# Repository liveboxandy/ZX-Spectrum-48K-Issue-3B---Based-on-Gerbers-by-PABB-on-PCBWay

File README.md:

# ZX-Spectrum 48K Issue 3B - Based on Gerbers by PABB on PCBWay

KiCAD created files for the ZX Spectrum 48K Issue 3B designed by Sinclair Research Ltd - Based on PABB Gerbers

Original Gerbers by PABB downloadable via PCBWay.

See https://www.pcbway.com/project/shareproject/ZX_Spectrum_48_Issue_3B_Redrawn.html

Only the gerbers are available on PCBWay. No Schematic.

Schematic created from available schematics with corrections using Service Guide mods and PCB layout. 

Where differences were seen the PCB layout took preference.

This was only done in order to create an assist in debugging.

I would NOT use these gerbers to get a PCB manufactured without a lot more checking first.

For the following ULA 6C001 make the following changes,

R47 to 1K,
R49 to 10K,
R56 to 1K,
R63 to 1K.

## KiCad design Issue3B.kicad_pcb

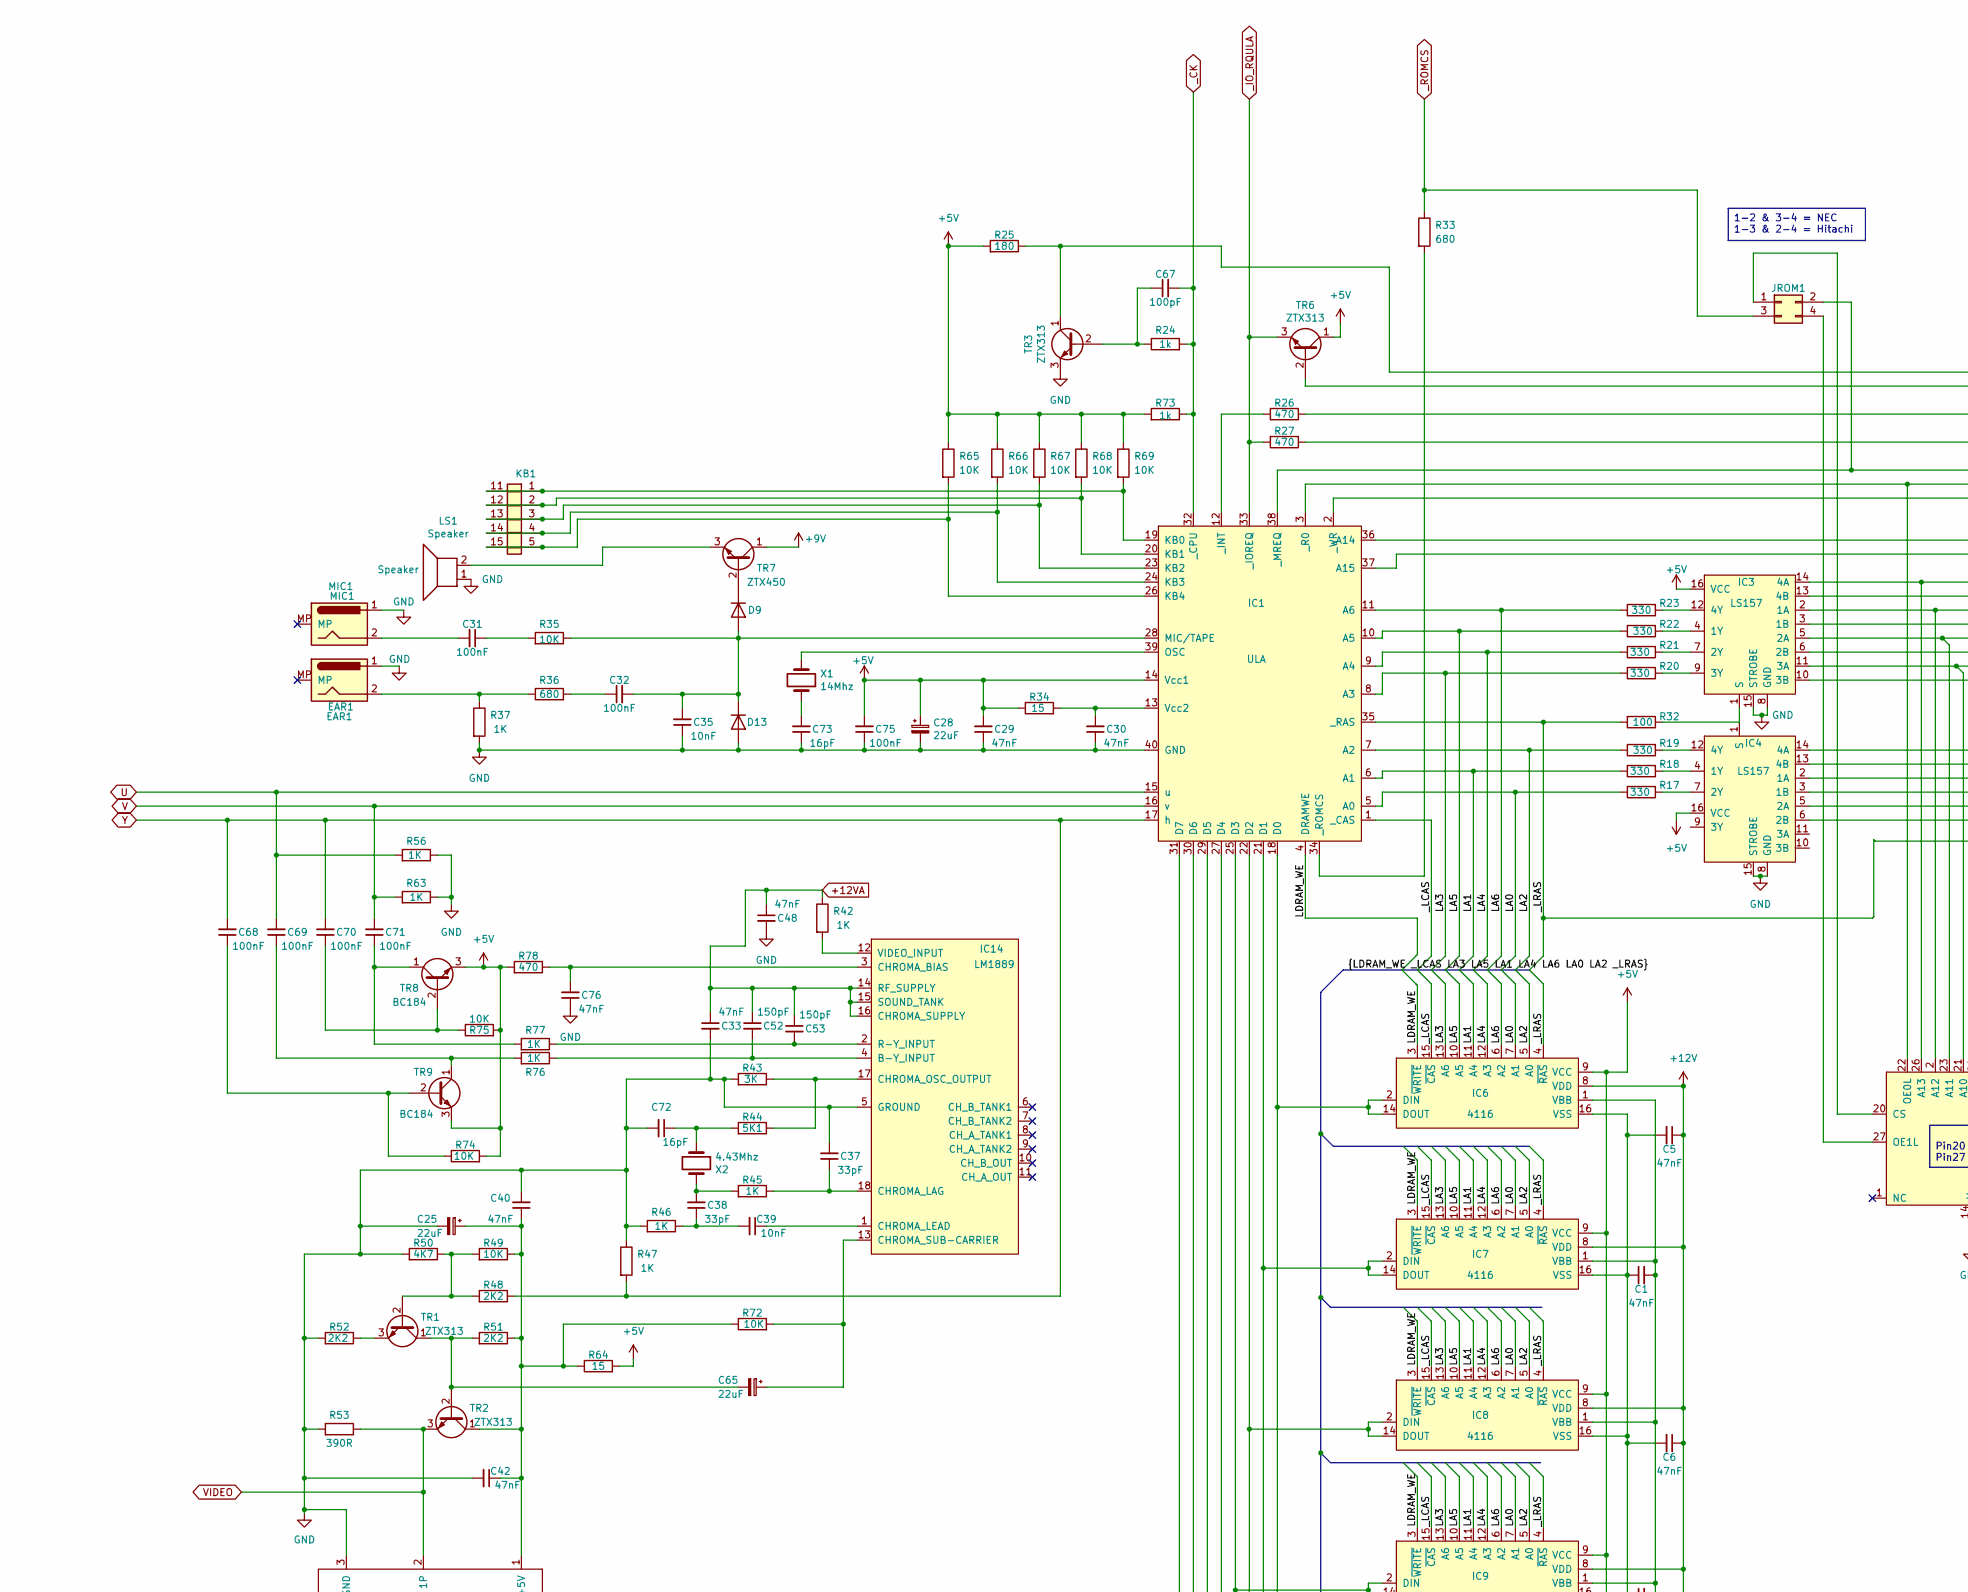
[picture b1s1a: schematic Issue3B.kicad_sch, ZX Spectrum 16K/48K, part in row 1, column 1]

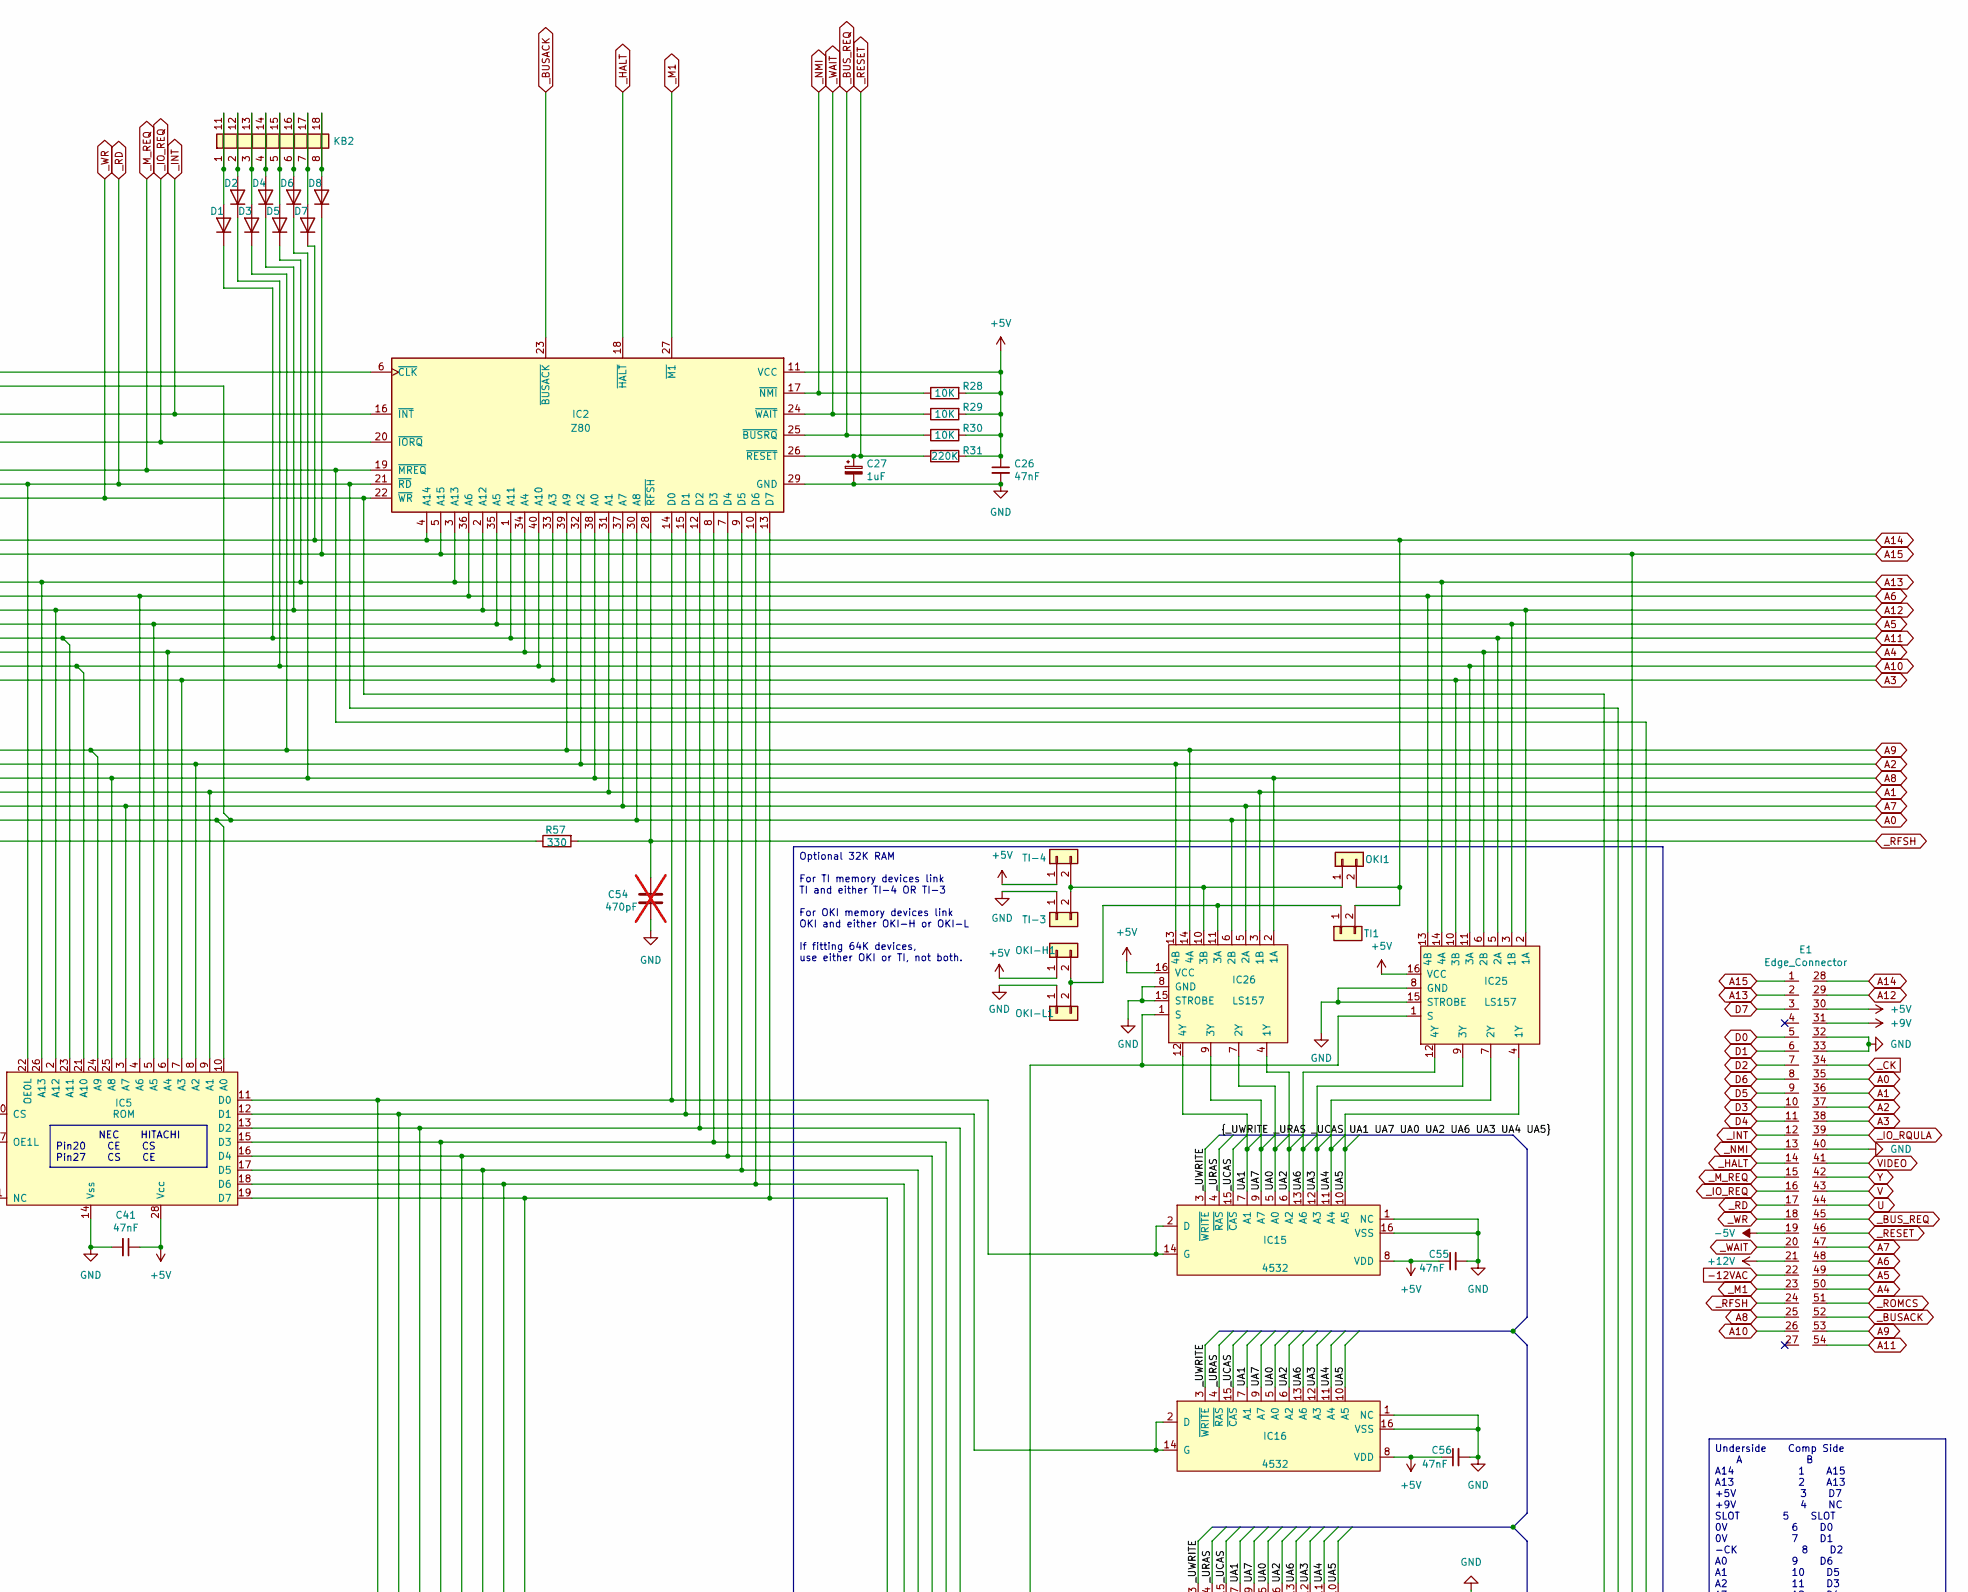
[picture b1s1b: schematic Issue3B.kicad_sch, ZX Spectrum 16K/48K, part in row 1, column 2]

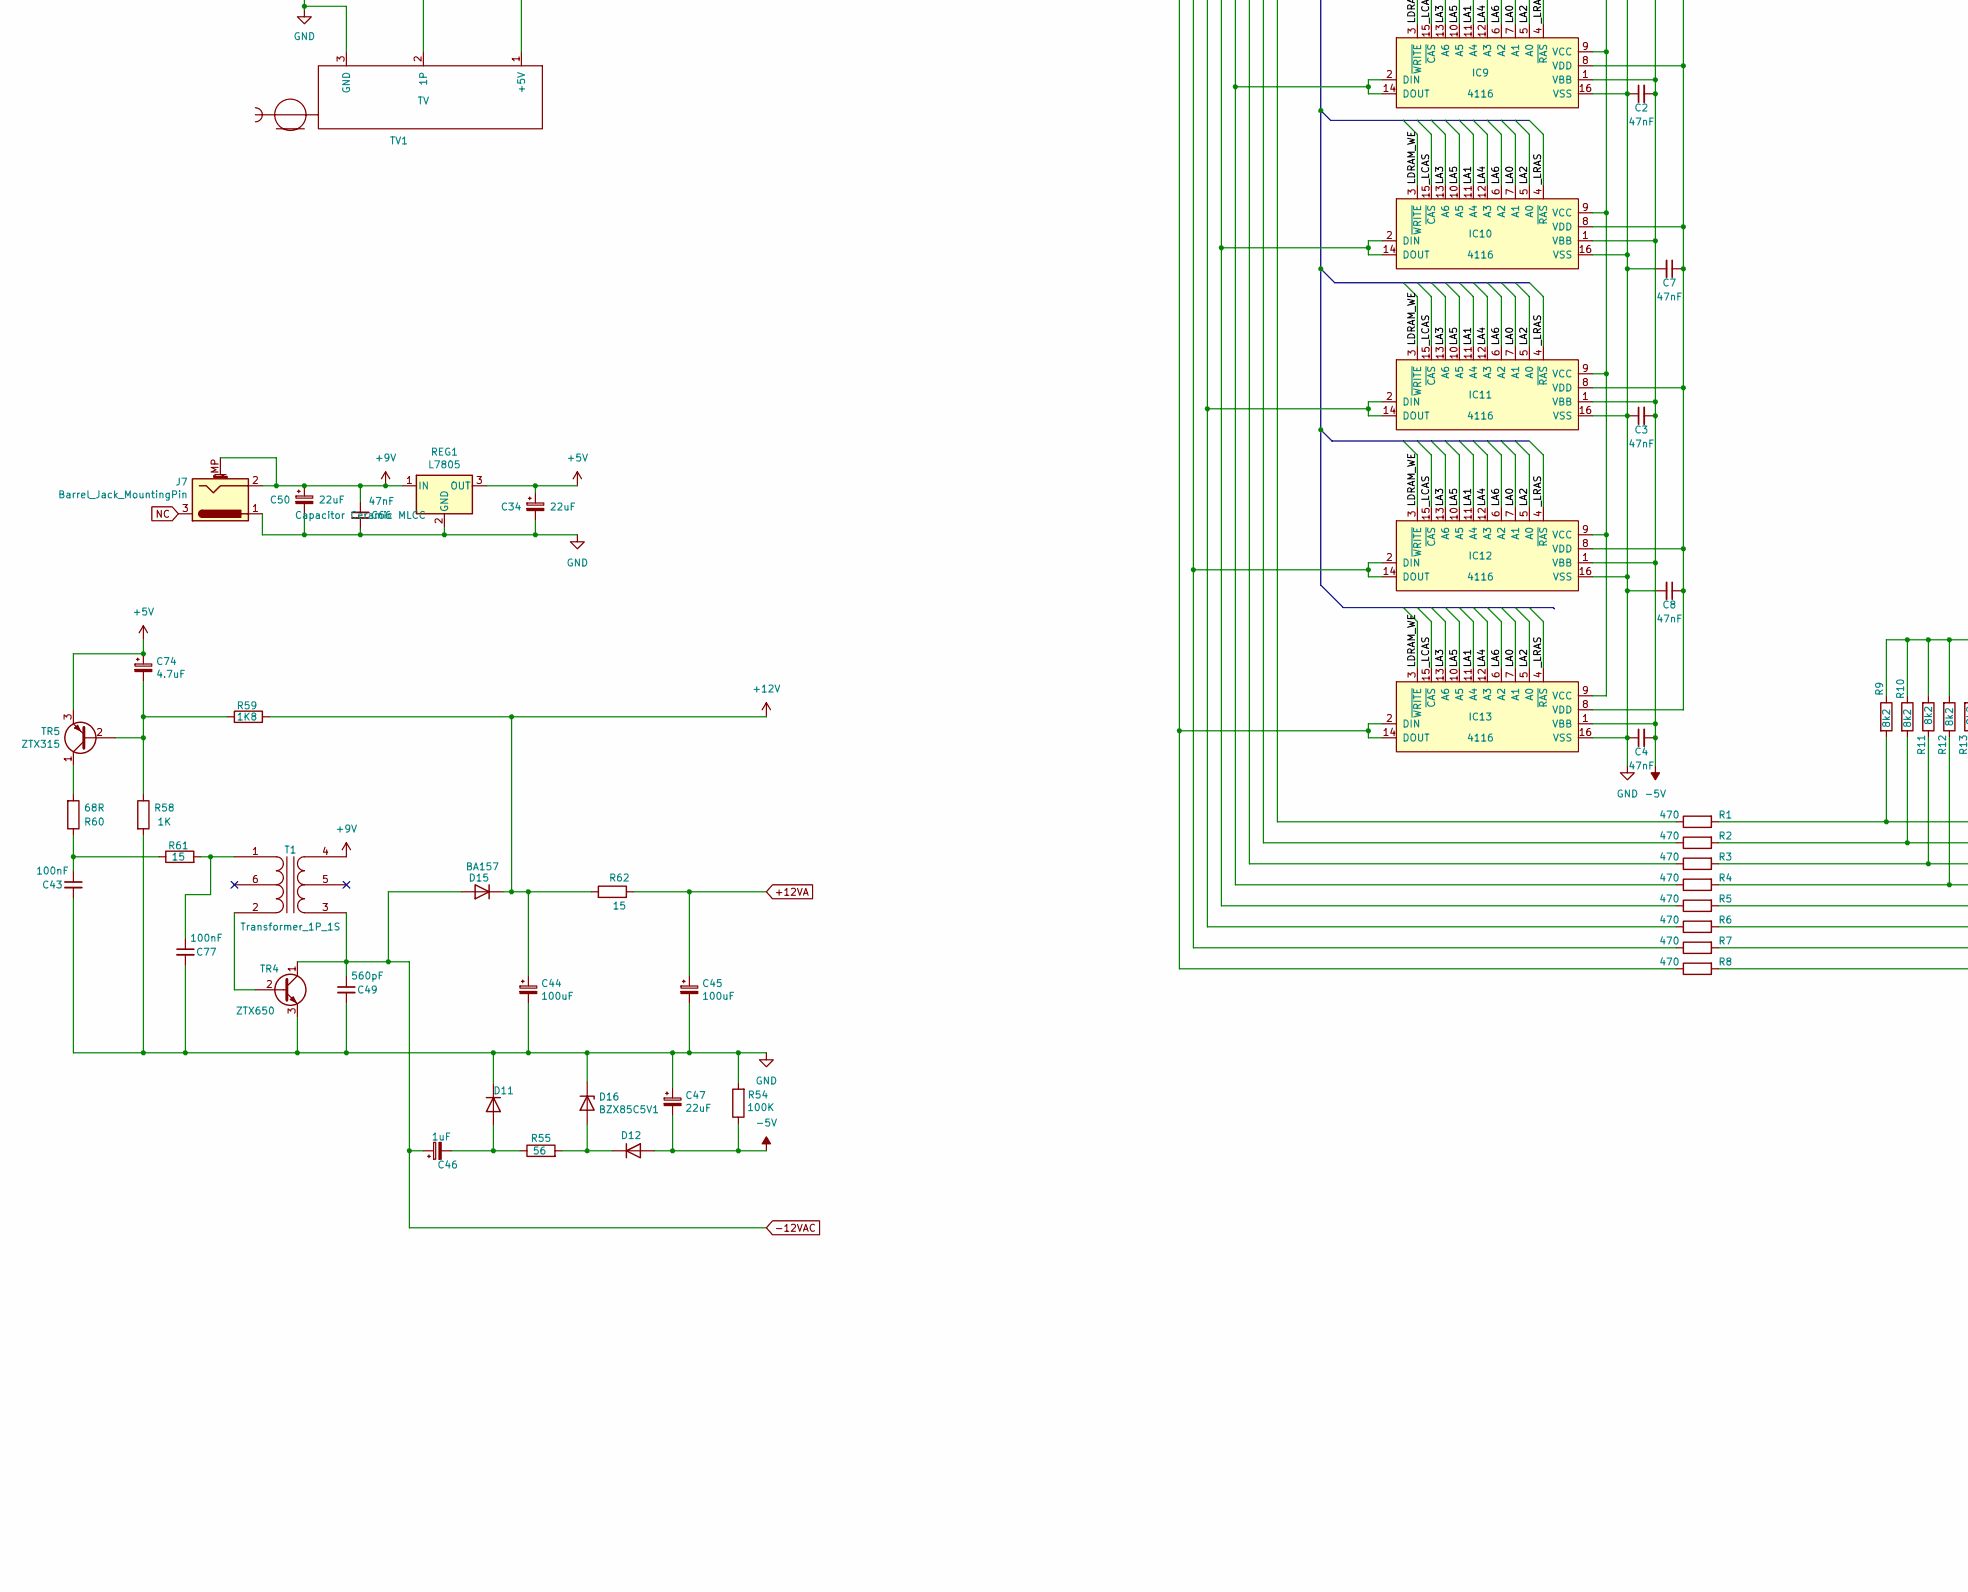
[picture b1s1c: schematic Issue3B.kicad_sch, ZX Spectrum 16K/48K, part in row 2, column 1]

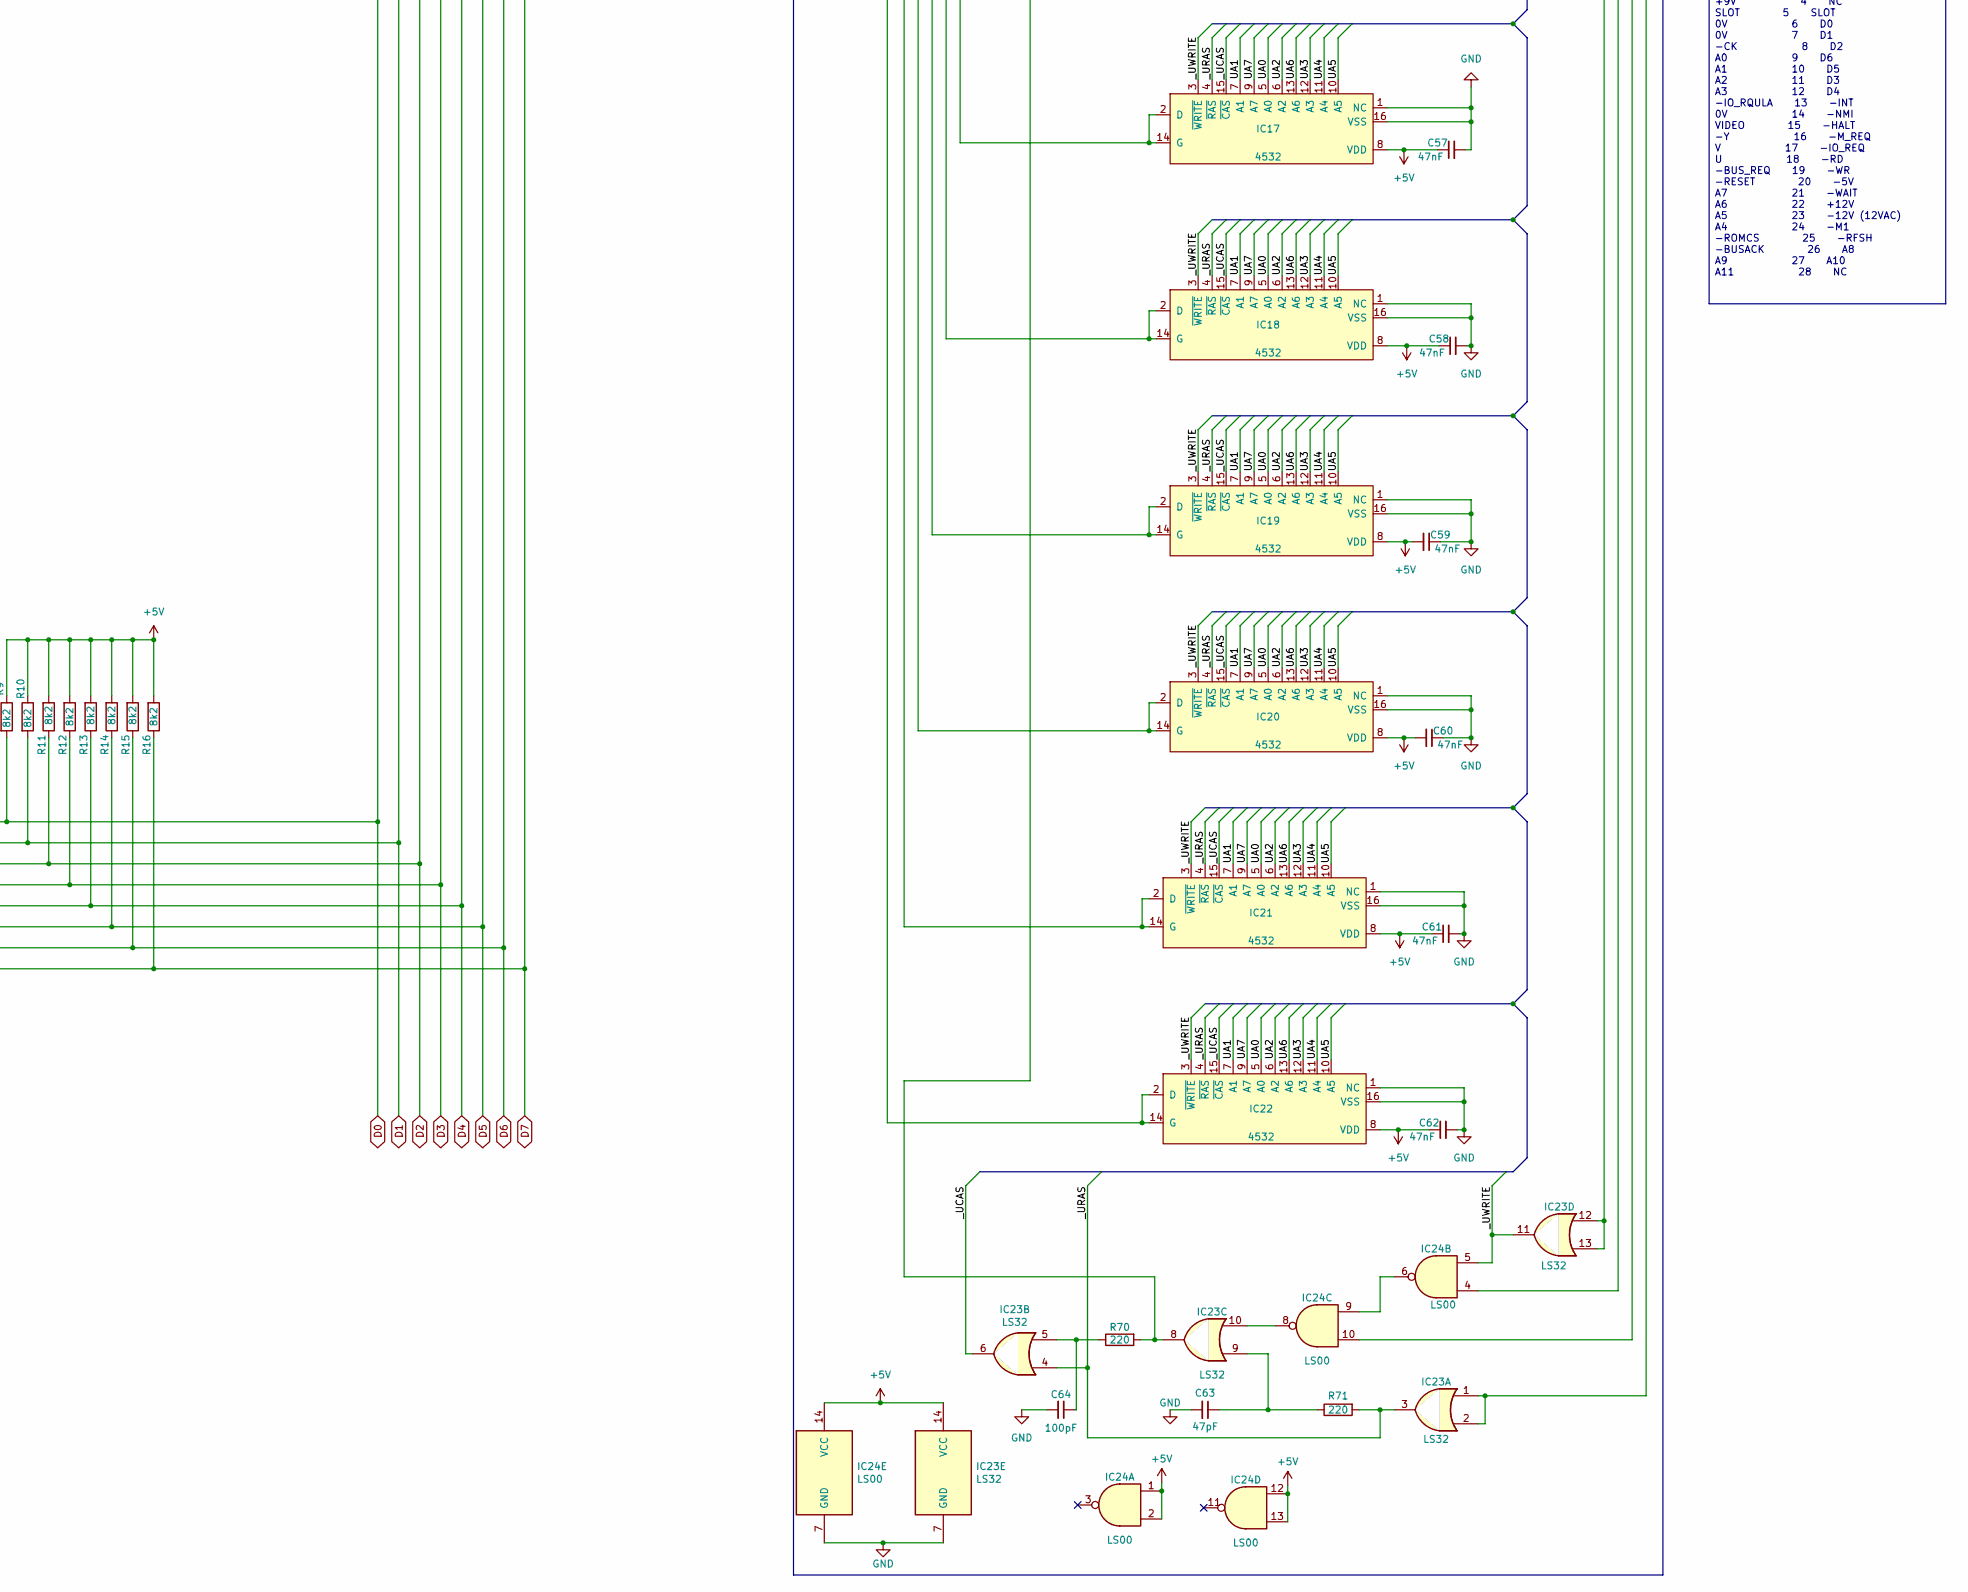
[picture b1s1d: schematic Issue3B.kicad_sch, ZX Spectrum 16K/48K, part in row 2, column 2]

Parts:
C1, C2, C3, C4, C5, C6, C7, C8, C26, C29, C30, C33, C40, C41, C42, C48, C55, C56, C57, C58, C59, C60, C61, C62, C66, C76: 47nF; C_Axial_L3.8mm_D2.6mm_P12.70mm_Horizontal
C25: 22uF; CP_Axial_L11.0mm_D6.0mm_P20.00mm_Horizontal
C27: 1uF; CP_Axial_L11.0mm_D6.0mm_P20.00mm_Horizontal
C28, C34, C47, C50, C65: 22uF; CP_Axial_L11.0mm_D6.0mm_P20.32mm_Horizontal
C31, C32: 100nF; C_Axial_L3.8mm_D2.6mm_P12.40mm_Horizontal
C35: 10nF; C_Axial_L3.8mm_D2.6mm_P12.40mm_Horizontal
C37, C38: 33pF; C_Axial_L3.8mm_D2.6mm_P12.70mm_Horizontal
C39: 10nF; C_Axial_L3.8mm_D2.6mm_P12.70mm_Horizontal
C43, C68, C69, C70, C71, C75, C77: 100nF; C_Axial_L3.8mm_D2.6mm_P12.70mm_Horizontal
C44, C45: 100uF; CP_Axial_L11.0mm_D6.0mm_P20.32mm_Horizontal
C46: 1uF; CP_Axial_L11.0mm_D6.0mm_P20.32mm_Horizontal
C49: 560pF; C_Axial_L3.8mm_D2.6mm_P12.70mm_Horizontal
C52, C53: 150pF; C_Axial_L3.8mm_D2.6mm_P12.70mm_Horizontal
C54: 470pF; C_Axial_L3.8mm_D2.6mm_P12.70mm_Horizontal; not fitted
C63: 47pF; C_Axial_L3.8mm_D2.6mm_P12.70mm_Horizontal
C64, C67: 100pF; C_Axial_L3.8mm_D2.6mm_P12.70mm_Horizontal
C72, C73: 16pF; C_Axial_L3.8mm_D2.6mm_P12.70mm_Horizontal
C74: 4.7uF; CP_Axial_L11.0mm_D6.0mm_P20.32mm_Horizontal
D1, D2, D3, D4, D5, D6, D7, D8, D9, D11, D12: 1N4148; D_DO-35_SOD27_P12.70mm_Horizontal
D13: 1N4148; D_DO-35_SOD27_P12.40mm_Horizontal
D15: BA157; D_DO-35_SOD27_P12.70mm_Horizontal
D16: BZX85C5V1; D_DO-35_SOD27_P12.70mm_Horizontal
E1: Edge_Connector; Edge Connector
EAR1: EAR1; 3.5mm_socket
IC1: ULA; DIP-40_W15.24mm_Socket
IC2: Z80; DIP-40_W15.24mm_Socket
IC3, IC4, IC25, IC26: LS157; DIP-16_W7.62mm_Socket
IC5: ROM; DIP-28_W15.24mm_Socket
IC6, IC7, IC8, IC9, IC10, IC11, IC12, IC13: 4116; DIP-16_W7.62mm_Socket
IC14: LM1889; DIP-18_W7.62mm_Socket
IC15, IC16, IC17, IC18, IC19, IC20, IC21, IC22: 4532; DIP-16_W7.62mm_Socket
IC23: LS32; DIP-14_W7.62mm_Socket
IC24: LS00; DIP-14_W7.62mm_Socket
J7: Barrel_Jack_MountingPin; BarrelJack_Horizontal
JROM1: JROM; ROM_WireLink
KB1: Keyboard5
KB2: Keyboard8
LS1: Speaker
MIC1: MIC1; 3.5mm_socket
OKI1: OKI; WireLink
OKI-H1: OKI-H; WireLink
OKI-L1: OKI-L; WireLink
R1, R2, R3, R4, R5, R6, R7, R8, R26, R27, R78: 470; R_Yageo_L3.6mm_D1.6mm_P12.70mm_Horizontal
R9, R10, R11, R12, R13, R14, R15, R16: 8k2; R_Yageo_L3.6mm_D1.6mm_P12.70mm_Horizontal
R17, R18, R19, R20, R21, R22, R23, R57: 330; R_Yageo_L3.6mm_D1.6mm_P12.70mm_Horizontal
R24, R73: 1k; R_Yageo_L3.6mm_D1.6mm_P12.70mm_Horizontal
R25: 180; R_Yageo_L3.6mm_D1.6mm_P12.70mm_Horizontal
R28, R29, R30, R49, R65, R66, R67, R68, R69, R72, R74, R75: 10K; R_Yageo_L3.6mm_D1.6mm_P12.70mm_Horizontal
R31: 220K; R_Yageo_L3.6mm_D1.6mm_P12.70mm_Horizontal
R32: 100; R_Yageo_L3.6mm_D1.6mm_P12.70mm_Horizontal
R33: 680; R_Yageo_L3.6mm_D1.6mm_P12.70mm_Horizontal
R34: 15; R_Axial_DIN0516_L15.5mm_D5.0mm_P22.60mm_Horizontal
R35: 10K; R_Yageo_L3.6mm_D1.6mm_P12.40mm_Horizontal
R36: 680; R_Yageo_L3.6mm_D1.6mm_P12.40mm_Horizontal
R37: 1K; R_Yageo_L3.6mm_D1.6mm_P12.40mm_Horizontal
R42, R45, R46, R47, R56, R58, R63, R76, R77: 1K; R_Yageo_L3.6mm_D1.6mm_P12.70mm_Horizontal
R43: 3K; R_Yageo_L3.6mm_D1.6mm_P12.70mm_Horizontal
R44: 5K1; R_Yageo_L3.6mm_D1.6mm_P12.70mm_Horizontal
R48, R51, R52: 2K2; R_Yageo_L3.6mm_D1.6mm_P12.70mm_Horizontal
R50: 4K7; R_Yageo_L3.6mm_D1.6mm_P12.70mm_Horizontal
R53: 390R; R_Yageo_L3.6mm_D1.6mm_P12.70mm_Horizontal
R54: 100K; R_Yageo_L3.6mm_D1.6mm_P12.70mm_Horizontal
R55: 56; R_Yageo_L3.6mm_D1.6mm_P12.70mm_Horizontal
R59: 1K8; R_Yageo_L3.6mm_D1.6mm_P12.70mm_Horizontal
R60: 68R; R_Yageo_L3.6mm_D1.6mm_P12.70mm_Horizontal
R61, R62, R64: 15; R_Yageo_L3.6mm_D1.6mm_P12.70mm_Horizontal
R70, R71: 220; R_Yageo_L3.6mm_D1.6mm_P12.70mm_Horizontal
REG1: L7805; TO-220-3_Horizontal_TabDown
T1: Transformer_1P_1S; Coil
TI1: TI; WireLink
TI-3: TI-3; WireLink
TI-4: TI-4; WireLink
TR1, TR2, TR3, TR6: ZTX313; TO-92Flat
TR4: ZTX650; TO-92Flat
TR5: ZTX315; TO-92Flat
TR7: ZTX450; TO-92Flat
TR8, TR9: BC184; TR9
TV1: TV; Modulator
X1: 14Mhz; X1
X2: 4.43Mhz; X2

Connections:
+5V: C26.1, C28.1, C29.2, C34.1, C41.1, C55.1, C56.1, C57.1, C58.1, C59.2, C60.2, C61.1, C62.1, C74.1, C75.2, E1.30, IC1.14 (Vcc1), IC2.11 (VCC), IC3.16 (VCC), IC4.16 (VCC), IC5.28 (Vcc), IC6.9 (VCC), IC7.9 (VCC), IC8.9 (VCC), IC9.9 (VCC), IC10.9 (VCC), IC11.9 (VCC), IC12.9 (VCC), IC13.9 (VCC), IC15.8 (VDD), IC16.8 (VDD), IC17.8 (VDD), IC18.8 (VDD), IC19.8 (VDD), IC20.8 (VDD), IC21.8 (VDD), IC22.8 (VDD), IC23.14 (VCC), IC24.1, IC24.2, IC24.12, IC24.13, IC24.14 (VCC), IC25.16 (VCC), IC26.16 (VCC), OKI-H1.1, R9.1, R10.1, R11.2, R12.2, R13.2, R14.2, R15.2, R16.2, R25.2, R28.2, R29.2, R30.2, R31.1, R34.1, R64.2, R65.1, R66.1, R67.1, R68.1, R69.1, R73.2, R74.2, R75.2, R78.2, REG1.3 (OUT), TI-4.1, TR5.3 (E), TR6.1 (C), TR8.3 (E), TR9.3 (E)
+9V: C50.1, C66.1, E1.31, J7.2, J7.MP (MountPin), REG1.1 (IN), T1.4 (SB), TR7.1 (C)
+12V: C5.1, C6.1, C7.1, C8.1, C44.1, D15.1 (K), E1.21, IC6.8 (VDD), IC7.8 (VDD), IC8.8 (VDD), IC9.8 (VDD), IC10.8 (VDD), IC11.8 (VDD), IC12.8 (VDD), IC13.8 (VDD), R59.2, R62.2
+12VA: C33.1, C45.1, C48.1, C52.1, C53.1, IC14.14 (RF_SUPPLY), IC14.15 (SOUND_TANK), IC14.16 (CHROMA_SUPPLY), R42.1, R62.1
-5V: C1.2, C2.2, C3.2, C4.2, C47.2, D12.2 (A), E1.19, IC6.1 (VBB), IC7.1 (VBB), IC8.1 (VBB), IC9.1 (VBB), IC10.1 (VBB), IC11.1 (VBB), IC12.1 (VBB), IC13.1 (VBB), R54.1
-12VAC: C46.1, C49.1, D15.2 (A), E1.22, T1.3 (SA), TR4.1 (C)
/LA0: IC1.5 (A0), IC6.7 (A1), IC7.7 (A1), IC8.7 (A1), IC9.7 (A1), IC10.7 (A1), IC11.7 (A1), IC12.7 (A1), IC13.7 (A1), R17.1
/LA1: IC1.6 (A1), IC6.11 (A4), IC7.11 (A4), IC8.11 (A4), IC9.11 (A4), IC10.11 (A4), IC11.11 (A4), IC12.11 (A4), IC13.11 (A4), R18.1
/LA2: IC1.7 (A2), IC6.5 (A0), IC7.5 (A0), IC8.5 (A0), IC9.5 (A0), IC10.5 (A0), IC11.5 (A0), IC12.5 (A0), IC13.5 (A0), R19.1
/LA3: IC1.8 (A3), IC6.13 (A6), IC7.13 (A6), IC8.13 (A6), IC9.13 (A6), IC10.13 (A6), IC11.13 (A6), IC12.13 (A6), IC13.13 (A6), R20.1
/LA4: IC1.9 (A4), IC6.12 (A3), IC7.12 (A3), IC8.12 (A3), IC9.12 (A3), IC10.12 (A3), IC11.12 (A3), IC12.12 (A3), IC13.12 (A3), R21.1
/LA5: IC1.10 (A5), IC6.10 (A5), IC7.10 (A5), IC8.10 (A5), IC9.10 (A5), IC10.10 (A5), IC11.10 (A5), IC12.10 (A5), IC13.10 (A5), R22.1
/LA6: IC1.11 (A6), IC6.6 (A2), IC7.6 (A2), IC8.6 (A2), IC9.6 (A2), IC10.6 (A2), IC11.6 (A2), IC12.6 (A2), IC13.6 (A2), R23.1
/LDRAM_WE: IC1.4 (DRAMWE), IC6.3 (~WRITE), IC7.3 (~WRITE), IC8.3 (~WRITE), IC9.3 (~WRITE), IC10.3 (~WRITE), IC11.3 (~WRITE), IC12.3 (~WRITE), IC13.3 (~WRITE)
/UA0: IC15.5 (A0), IC16.5 (A0), IC17.5 (A0), IC18.5 (A0), IC19.5 (A0), IC20.5 (A0), IC21.5 (A0), IC22.5 (A0), IC26.7 (2Y)
/UA1: IC15.7 (A1), IC16.7 (A1), IC17.7 (A1), IC18.7 (A1), IC19.7 (A1), IC20.7 (A1), IC21.7 (A1), IC22.7 (A1), IC26.12 (4Y)
/UA2: IC15.6 (A2), IC16.6 (A2), IC17.6 (A2), IC18.6 (A2), IC19.6 (A2), IC20.6 (A2), IC21.6 (A2), IC22.6 (A2), IC26.4 (1Y)
/UA3: IC15.12 (A3), IC16.12 (A3), IC17.12 (A3), IC18.12 (A3), IC19.12 (A3), IC20.12 (A3), IC21.12 (A3), IC22.12 (A3), IC25.9 (3Y)
/UA4: IC15.11 (A4), IC16.11 (A4), IC17.11 (A4), IC18.11 (A4), IC19.11 (A4), IC20.11 (A4), IC21.11 (A4), IC22.11 (A4), IC25.7 (2Y)
/UA5: IC15.10 (A5), IC16.10 (A5), IC17.10 (A5), IC18.10 (A5), IC19.10 (A5), IC20.10 (A5), IC21.10 (A5), IC22.10 (A5), IC25.4 (1Y)
/UA6: IC15.13 (A6), IC16.13 (A6), IC17.13 (A6), IC18.13 (A6), IC19.13 (A6), IC20.13 (A6), IC21.13 (A6), IC22.13 (A6), IC25.12 (4Y)
/UA7: IC15.9 (A7), IC16.9 (A7), IC17.9 (A7), IC18.9 (A7), IC19.9 (A7), IC20.9 (A7), IC21.9 (A7), IC22.9 (A7), IC26.9 (3Y)
/_LCAS: IC1.1 (_CAS), IC6.15 (~CAS), IC7.15 (~CAS), IC8.15 (~CAS), IC9.15 (~CAS), IC10.15 (~CAS), IC11.15 (~CAS), IC12.15 (~CAS), IC13.15 (~CAS)
/_LRAS: IC1.35 (_RAS), IC6.4 (~RAS), IC7.4 (~RAS), IC8.4 (~RAS), IC9.4 (~RAS), IC10.4 (~RAS), IC11.4 (~RAS), IC12.4 (~RAS), IC13.4 (~RAS), R32.2, R57.1
/_UCAS: IC15.15 (~CAS), IC16.15 (~CAS), IC17.15 (~CAS), IC18.15 (~CAS), IC19.15 (~CAS), IC20.15 (~CAS), IC21.15 (~CAS), IC22.15 (~CAS), IC23.6
/_URAS: IC15.4 (~RAS), IC16.4 (~RAS), IC17.4 (~RAS), IC18.4 (~RAS), IC19.4 (~RAS), IC20.4 (~RAS), IC21.4 (~RAS), IC22.4 (~RAS), IC23.3, IC23.4, R71.2
/_UWRITE: IC15.3 (~WRITE), IC16.3 (~WRITE), IC17.3 (~WRITE), IC18.3 (~WRITE), IC19.3 (~WRITE), IC20.3 (~WRITE), IC21.3 (~WRITE), IC22.3 (~WRITE), IC23.11, IC24.5
A0: E1.35, IC2.30 (A8), IC4.6 (2B), IC5.10 (A0), IC26.6 (2B), TR6.2 (B)
A1: E1.36, IC2.31 (A1), IC4.3 (1B), IC5.9 (A1), IC26.3 (1B)
A2: E1.37, IC2.32 (A2), IC4.13 (4B), IC5.8 (A2), IC26.13 (4B)
A3: E1.38, IC2.33 (A3), IC3.10 (3B), IC5.7 (A3), IC25.10 (3B)
A4: E1.50, IC2.34 (A4), IC3.6 (2B), IC5.6 (A4), IC25.6 (2B)
A5: E1.49, IC2.35 (A5), IC3.3 (1B), IC5.5 (A5), IC25.3 (1B)
A6: E1.48, IC2.36 (A6), IC3.13 (4B), IC5.4 (A6), IC25.13 (4B)
A7: E1.47, IC2.37 (A7), IC4.5 (2A), IC5.3 (A7), IC26.5 (2A)
A8: D6.1 (K), E1.25, IC2.38 (A0), IC4.2 (1A), IC5.25 (A8), IC26.2 (1A)
A9: D3.1 (K), E1.53, IC2.39 (A9), IC4.14 (4A), IC5.24 (A9), IC26.14 (4A)
A10: D2.1 (K), E1.26, IC2.40 (A10), IC3.11 (3A), IC5.21 (A10), IC25.11 (3A)
A11: D1.1 (K), E1.54, IC2.1 (A11), IC3.5 (2A), IC5.23 (A11), IC25.5 (2A)
A12: D4.1 (K), E1.29, IC2.2 (A12), IC3.2 (1A), IC5.2 (A12), IC25.2 (1A)
A13: D5.1 (K), E1.2, IC2.3 (A13), IC3.14 (4A), IC5.26 (A13), IC25.14 (4A)
A14: D7.1 (K), E1.28, IC1.36 (A14), IC2.4 (A14), OKI1.2, TI1.2
A15: D8.1 (K), E1.1, IC1.37 (A15), IC2.5 (A15), IC24.10
D0: E1.5, IC2.14 (D0), IC5.11 (D0), IC15.2 (D), IC15.14 (G), R1.2, R9.2
D1: E1.6, IC2.15 (D1), IC5.12 (D1), IC16.2 (D), IC16.14 (G), R2.2, R10.2
D2: E1.7, IC2.12 (D2), IC5.13 (D2), IC17.2 (D), IC17.14 (G), R3.2, R11.1
D3: E1.10, IC2.8 (D3), IC5.15 (D3), IC18.2 (D), IC18.14 (G), R4.2, R12.1
D4: E1.11, IC2.7 (D4), IC5.16 (D4), IC19.2 (D), IC19.14 (G), R5.2, R13.1
D5: E1.9, IC2.9 (D5), IC5.17 (D5), IC20.2 (D), IC20.14 (G), R6.2, R14.1
D6: E1.8, IC2.10 (D6), IC5.18 (D6), IC21.2 (D), IC21.14 (G), R7.2, R15.1
D7: E1.3, IC2.13 (D7), IC5.19 (D7), IC22.2 (D), IC22.14 (G), R8.2, R16.1
GND: C1.1, C2.1, C3.1, C4.1, C5.2, C6.2, C7.2, C8.2, C25.2, C26.2, C27.2, C28.2, C29.1, C30.1, C33.2, C34.2, C35.1, C37.2, C40.2, C41.2, C42.2, C43.2, C44.2, C45.2, C47.1, C48.2, C49.2, C50.2, C54.2, C55.2, C56.2, C57.2, C58.2, C59.1, C60.1, C61.2, C62.2, C63.2, C64.2, C66.2, C72.2, C73.1, C75.1, C76.1, C77.2, D11.1 (K), D13.2 (A), D16.1 (K), E1.32, E1.33, E1.40, EAR1.1, IC1.40 (GND), IC2.29 (GND), IC3.8 (GND), IC3.15 (STROBE), IC4.8 (GND), IC4.15 (STROBE), IC5.14 (Vss), IC6.16 (VSS), IC7.16 (VSS), IC8.16 (VSS), IC9.16 (VSS), IC10.16 (VSS), IC11.16 (VSS), IC12.16 (VSS), IC13.16 (VSS), IC14.5 (GROUND), IC15.1 (NC), IC15.16 (VSS), IC16.1 (NC), IC16.16 (VSS), IC17.1 (NC), IC17.16 (VSS), IC18.1 (NC), IC18.16 (VSS), IC19.1 (NC), IC19.16 (VSS), IC20.1 (NC), IC20.16 (VSS), IC21.1 (NC), IC21.16 (VSS), IC22.1 (NC), IC22.16 (VSS), IC23.7 (GND), IC24.7 (GND), IC25.8 (GND), IC25.15 (STROBE), IC26.8 (GND), IC26.15 (STROBE), J7.1, LS1.1, MIC1.1, OKI-L1.1, R37.2, R43.2, R46.2, R47.1, R50.2, R52.2, R53.2, R54.2, R56.1, R58.2, R63.1, REG1.2 (GND), TI-3.1, TR3.3 (E), TR4.3 (E), TV1.3 (GND)
NC: J7.3 (MP2)
unnamed: C31.1, R35.2
unnamed: C31.2, MIC1.2
unnamed: C32.1, R36.2
unnamed: C38.1, C39.2, R46.1
unnamed: C38.2, R45.2, X2.2
unnamed: C43.1, R60.1, R61.1
unnamed: C63.1, IC23.9, R71.1
unnamed: C64.1, IC23.5, R70.1
unnamed: C72.1, R44.2, X2.1
unnamed: C73.2, X1.1
unnamed: D1.2 (A), KB2.1, KB2.11 (Pin_1A)
unnamed: D2.2 (A), KB2.2, KB2.12 (Pin_2A)
unnamed: D3.2 (A), KB2.3, KB2.13 (Pin_3A)
unnamed: D4.2 (A), KB2.4, KB2.14 (Pin_4A)
unnamed: D5.2 (A), KB2.5, KB2.15 (Pin_5A)
unnamed: D6.2 (A), KB2.6, KB2.16 (Pin_6A)
unnamed: D7.2 (A), KB2.7, KB2.17 (Pin_7A)
unnamed: D8.2 (A), KB2.8, KB2.18 (Pin_8A)
unnamed: D9.1 (K), TR7.2 (B)
unnamed: C46.2, D11.2 (A), R55.1
unnamed: D12.1 (K), D16.2 (A), R55.2
unnamed: C32.2, C35.2, D9.2 (A), D13.1 (K), IC1.28 (MIC/TAPE), R35.1
unnamed: EAR1.2, R36.1, R37.1
unnamed: IC1.18 (D0), IC6.2 (DIN), IC6.14 (DOUT), R1.1
unnamed: IC1.21 (D1), IC7.2 (DIN), IC7.14 (DOUT), R2.1
unnamed: IC1.22 (D2), IC8.2 (DIN), IC8.14 (DOUT), R3.1
unnamed: IC1.25 (D3), IC9.2 (DIN), IC9.14 (DOUT), R4.1
unnamed: IC1.27 (D4), IC10.2 (DIN), IC10.14 (DOUT), R5.1
unnamed: IC1.29 (D5), IC11.2 (DIN), IC11.14 (DOUT), R6.1
unnamed: IC1.30 (D6), IC12.2 (DIN), IC12.14 (DOUT), R7.1
unnamed: IC1.31 (D7), IC13.2 (DIN), IC13.14 (DOUT), R8.1
unnamed: IC1.19 (KB0), KB1.1, KB1.11 (A1), R69.2
unnamed: IC1.20 (KB1), KB1.2, KB1.12 (2A), R68.2
unnamed: IC1.23 (KB2), KB1.3, KB1.13 (3A), R67.2
unnamed: IC1.24 (KB3), KB1.4, KB1.14 (4A), R66.2
unnamed: IC1.26 (KB4), KB1.5, KB1.15 (5A), R65.2
unnamed: IC1.39 (OSC), X1.2
unnamed: C30.2, IC1.13 (Vcc2), R34.2
unnamed: IC1.12 (_INT), R26.1
unnamed: IC1.34 (_ROMCS), R33.2
unnamed: IC2.6 (~CLK), R25.1, TR3.1 (C)
unnamed: IC3.4 (1Y), R22.2
unnamed: IC3.7 (2Y), R21.2
unnamed: IC3.9 (3Y), R20.2
unnamed: IC3.12 (4Y), R23.2
unnamed: IC3.1 (S), IC4.1 (S), R32.1
unnamed: IC4.4 (1Y), R18.2
unnamed: IC4.7 (2Y), R17.2
unnamed: IC4.12 (4Y), R19.2
unnamed: IC5.20 (CS), JROM1.1
unnamed: IC5.27 (OE1L), JROM1.4
unnamed: C52.2, IC14.4 (B-Y_INPUT), R76.1
unnamed: C76.2, IC14.3 (CHROMA_BIAS), R78.1
unnamed: C37.1, IC14.18 (CHROMA_LAG), R45.1
unnamed: C39.1, IC14.1 (CHROMA_LEAD)
unnamed: IC14.17 (CHROMA_OSC_OUTPUT), R43.1, R44.1
unnamed: C65.1, IC14.13 (CHROMA_SUB-CARRIER), R72.2
unnamed: C53.2, IC14.2 (R-Y_INPUT), R77.1
unnamed: IC14.12 (VIDEO_INPUT), R42.2
unnamed: IC23.10, IC24.8
unnamed: IC24.6, IC24.9
unnamed: IC23.8, IC25.1 (S), IC26.1 (S), R70.2
unnamed: IC26.11 (3A), OKI-H1.2, OKI-L1.2, TI1.1
unnamed: IC26.10 (3B), OKI1.1, TI-3.2, TI-4.2
unnamed: C77.1, R61.2, T1.1 (AA)
unnamed: T1.2 (AB), TR4.2 (B)
unnamed: R48.2, R49.2, R50.1, TR1.2 (B)
unnamed: C65.2, R51.2, TR1.1 (C), TR2.2 (B)
unnamed: R52.1, TR1.3 (E)
unnamed: C25.1, C40.1, C42.1, R49.1, R51.1, R64.1, R72.1, TR2.1 (C), TV1.1 (+5V)
unnamed: C67.1, R24.1, TR3.2 (B)
unnamed: C74.2, R58.1, R59.1, TR5.2 (B)
unnamed: R60.2, TR5.1 (C)
unnamed: LS1.2, TR7.3 (E)
unnamed: C70.1, R75.1, TR8.2 (B)
unnamed: C71.1, R77.2, TR8.1 (C)
unnamed: C68.1, R74.1, TR9.2 (B)
unnamed: C69.1, R76.2, TR9.1 (C)
U: C69.2, E1.44, IC1.15 (u), R56.2
V: C71.2, E1.43, IC1.16 (v), R63.2
VIDEO: E1.41, R53.1, TR2.3 (E), TV1.2 (1P)
Y: C68.2, C70.2, E1.42, IC1.17 (h), R47.2, R48.1
_BUSACK: E1.52, IC2.23 (~BUSACK)
_BUS_REQ: E1.45, IC2.25 (~BUSRQ), R30.1
_CK: C67.2, E1.34, IC1.32 (_CPU), R24.2, R73.1
_HALT: E1.14, IC2.18 (~HALT)
_INT: E1.12, IC2.16 (~INT), R26.2
_IO_REQ: E1.16, IC2.20 (~IORQ), R27.2
_IO_RQULA: E1.39, IC1.33 (_IOREQ), R27.1, TR6.3 (E)
_M1: E1.23, IC2.27 (~M1)
_M_REQ: E1.15, IC1.38 (_MREQ), IC2.19 (~MREQ), IC23.1, IC23.2, JROM1.2
_NMI: E1.13, IC2.17 (~NMI), R28.1
_RD: E1.17, IC1.3 (_R0), IC2.21 (~RD), IC5.22 (OE0L), IC24.4
_RESET: C27.1, E1.46, IC2.26 (~RESET), R31.2
_RFSH: C54.1, E1.24, IC2.28 (~RFSH), R57.2
_ROMCS: E1.51, JROM1.3, R33.1
_WAIT: E1.20, IC2.24 (~WAIT), R29.1
_WR: E1.18, IC1.2 (_WR), IC2.22 (~WR), IC23.12, IC23.13

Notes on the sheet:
Optional 32K RAM For TI memory devices link TI and either TI-4 OR TI-3 For OKI memory devices link OKI and either OKI-H or OKI-L If fitting 64K devices, use either OKI or TI, not both.
NEC HITACHI Pin20 CE CS Pin27 CS CE
Underside Comp Side A B A14 1 A15 A13 2 A13 +5V 3 D7 +9V 4 NC SLOT 5 SLOT 0V 6 D0 0V 7 D1 -CK 8 D2 A0 9 D6 A1 10 D5 A2 11 D3 A3 12 D4 -IO_RQULA 13 -INT 0V 14 -NMI VIDEO 15 -HALT -Y 16 -M_REQ V 17 -IO_REQ U 18 -RD -BUS_REQ 19 -WR -RESET 20 -5V A7 21 -WAIT A6 22 +12V A5 23 -12V (12VAC) A4 24 -M1 -ROM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
1-2 & 3-4 = NEC 1-3 & 2-4 = Hitachi

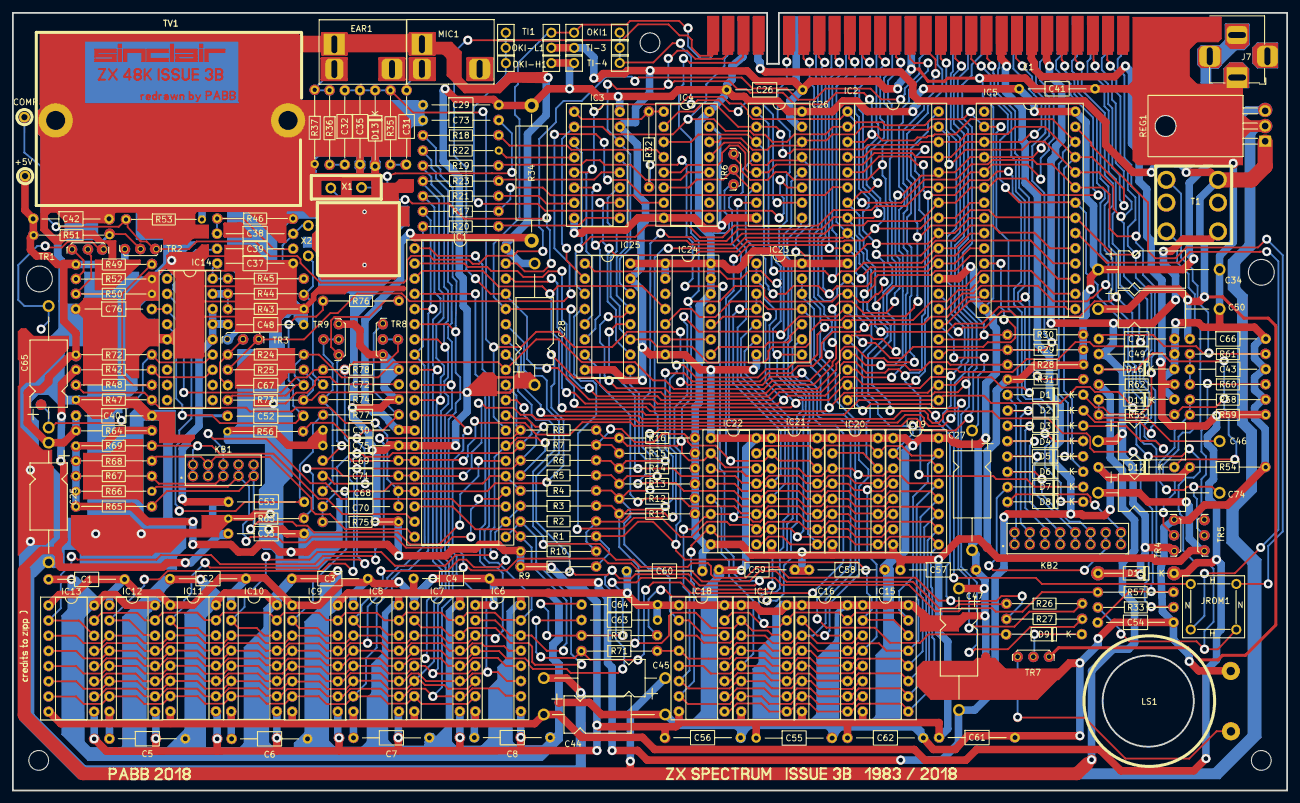
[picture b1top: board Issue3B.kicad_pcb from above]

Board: 2 copper layers, 213.1 x 130.0 mm, 201 parts (0 on the bottom side), 150 nets.
